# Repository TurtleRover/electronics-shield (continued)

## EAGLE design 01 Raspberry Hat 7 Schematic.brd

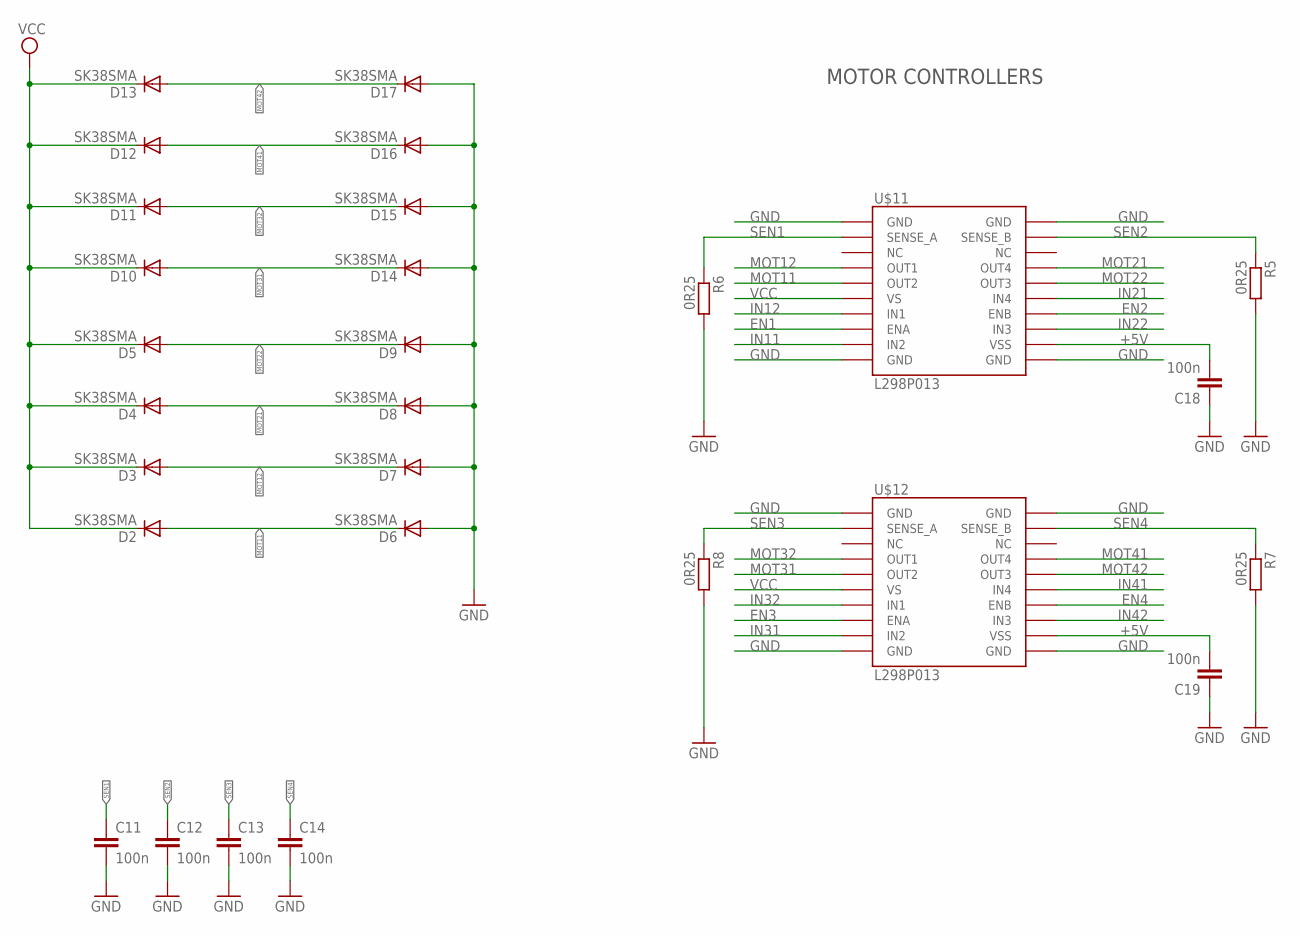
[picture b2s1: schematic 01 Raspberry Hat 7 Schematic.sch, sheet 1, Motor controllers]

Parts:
C11, C12, C13, C14, C18, C19: 100n; C0603K
D2, D3, D4, D5, D6, D7, D8, D9, D10, D11, D12, D13, D14, D15, D16, D17: SK38SMA; SOD123
R5, R6, R7, R8: 0R25; R2512
U$11, U$12: L298P013; POWERSO20

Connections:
+5V: C18.2, C19.2, U$11.12 (VSS), U$12.12 (VSS); also elsewhere on the board
EN1: U$11.8 (ENA); also elsewhere on the board
EN2: U$11.14 (ENB); also elsewhere on the board
EN3: U$12.8 (ENA); also elsewhere on the board
EN4: U$12.14 (ENB); also elsewhere on the board
GND: C11.2, C12.2, C13.2, C14.2, C18.1, C19.1, D6.A, D7.A, D8.A, D9.A, D14.A, D15.A, D16.A, D17.A, R5.2, R6.2, R7.2, R8.2, U$11.1 (GND), U$11.10 (GND), U$11.11 (GND), U$11.20 (GND), U$12.1 (GND), U$12.10 (GND), U$12.11 (GND), U$12.20 (GND); also elsewhere on the board
IN11: U$11.9 (IN2); also elsewhere on the board
IN12: U$11.7 (IN1); also elsewhere on the board
IN21: U$11.15 (IN4); also elsewhere on the board
IN22: U$11.13 (IN3); also elsewhere on the board
IN31: U$12.9 (IN2); also elsewhere on the board
IN32: U$12.7 (IN1); also elsewhere on the board
IN41: U$12.15 (IN4); also elsewhere on the board
IN42: U$12.13 (IN3); also elsewhere on the board
MOT11: D2.A, D6.C, U$11.5 (OUT2); also elsewhere on the board
MOT12: D3.A, D7.C, U$11.4 (OUT1); also elsewhere on the board
MOT21: D4.A, D8.C, U$11.17 (OUT4); also elsewhere on the board
MOT22: D5.A, D9.C, U$11.16 (OUT3); also elsewhere on the board
MOT31: D10.A, D14.C, U$12.5 (OUT2); also elsewhere on the board
MOT32: D11.A, D15.C, U$12.4 (OUT1); also elsewhere on the board
MOT41: D12.A, D16.C, U$12.17 (OUT4); also elsewhere on the board
MOT42: D13.A, D17.C, U$12.16 (OUT3); also elsewhere on the board
SEN1: C11.1, R6.1, U$11.2 (SENSE_A); also elsewhere on the board
SEN2: C12.1, R5.1, U$11.19 (SENSE_B); also elsewhere on the board
SEN3: C13.1, R8.1, U$12.2 (SENSE_A); also elsewhere on the board
SEN4: C14.1, R7.1, U$12.19 (SENSE_B); also elsewhere on the board
VCC: D2.C, D3.C, D4.C, D5.C, D10.C, D11.C, D12.C, D13.C, U$11.6 (VS), U$12.6 (VS); also elsewhere on the board

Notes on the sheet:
MOTOR CONTROLLERS

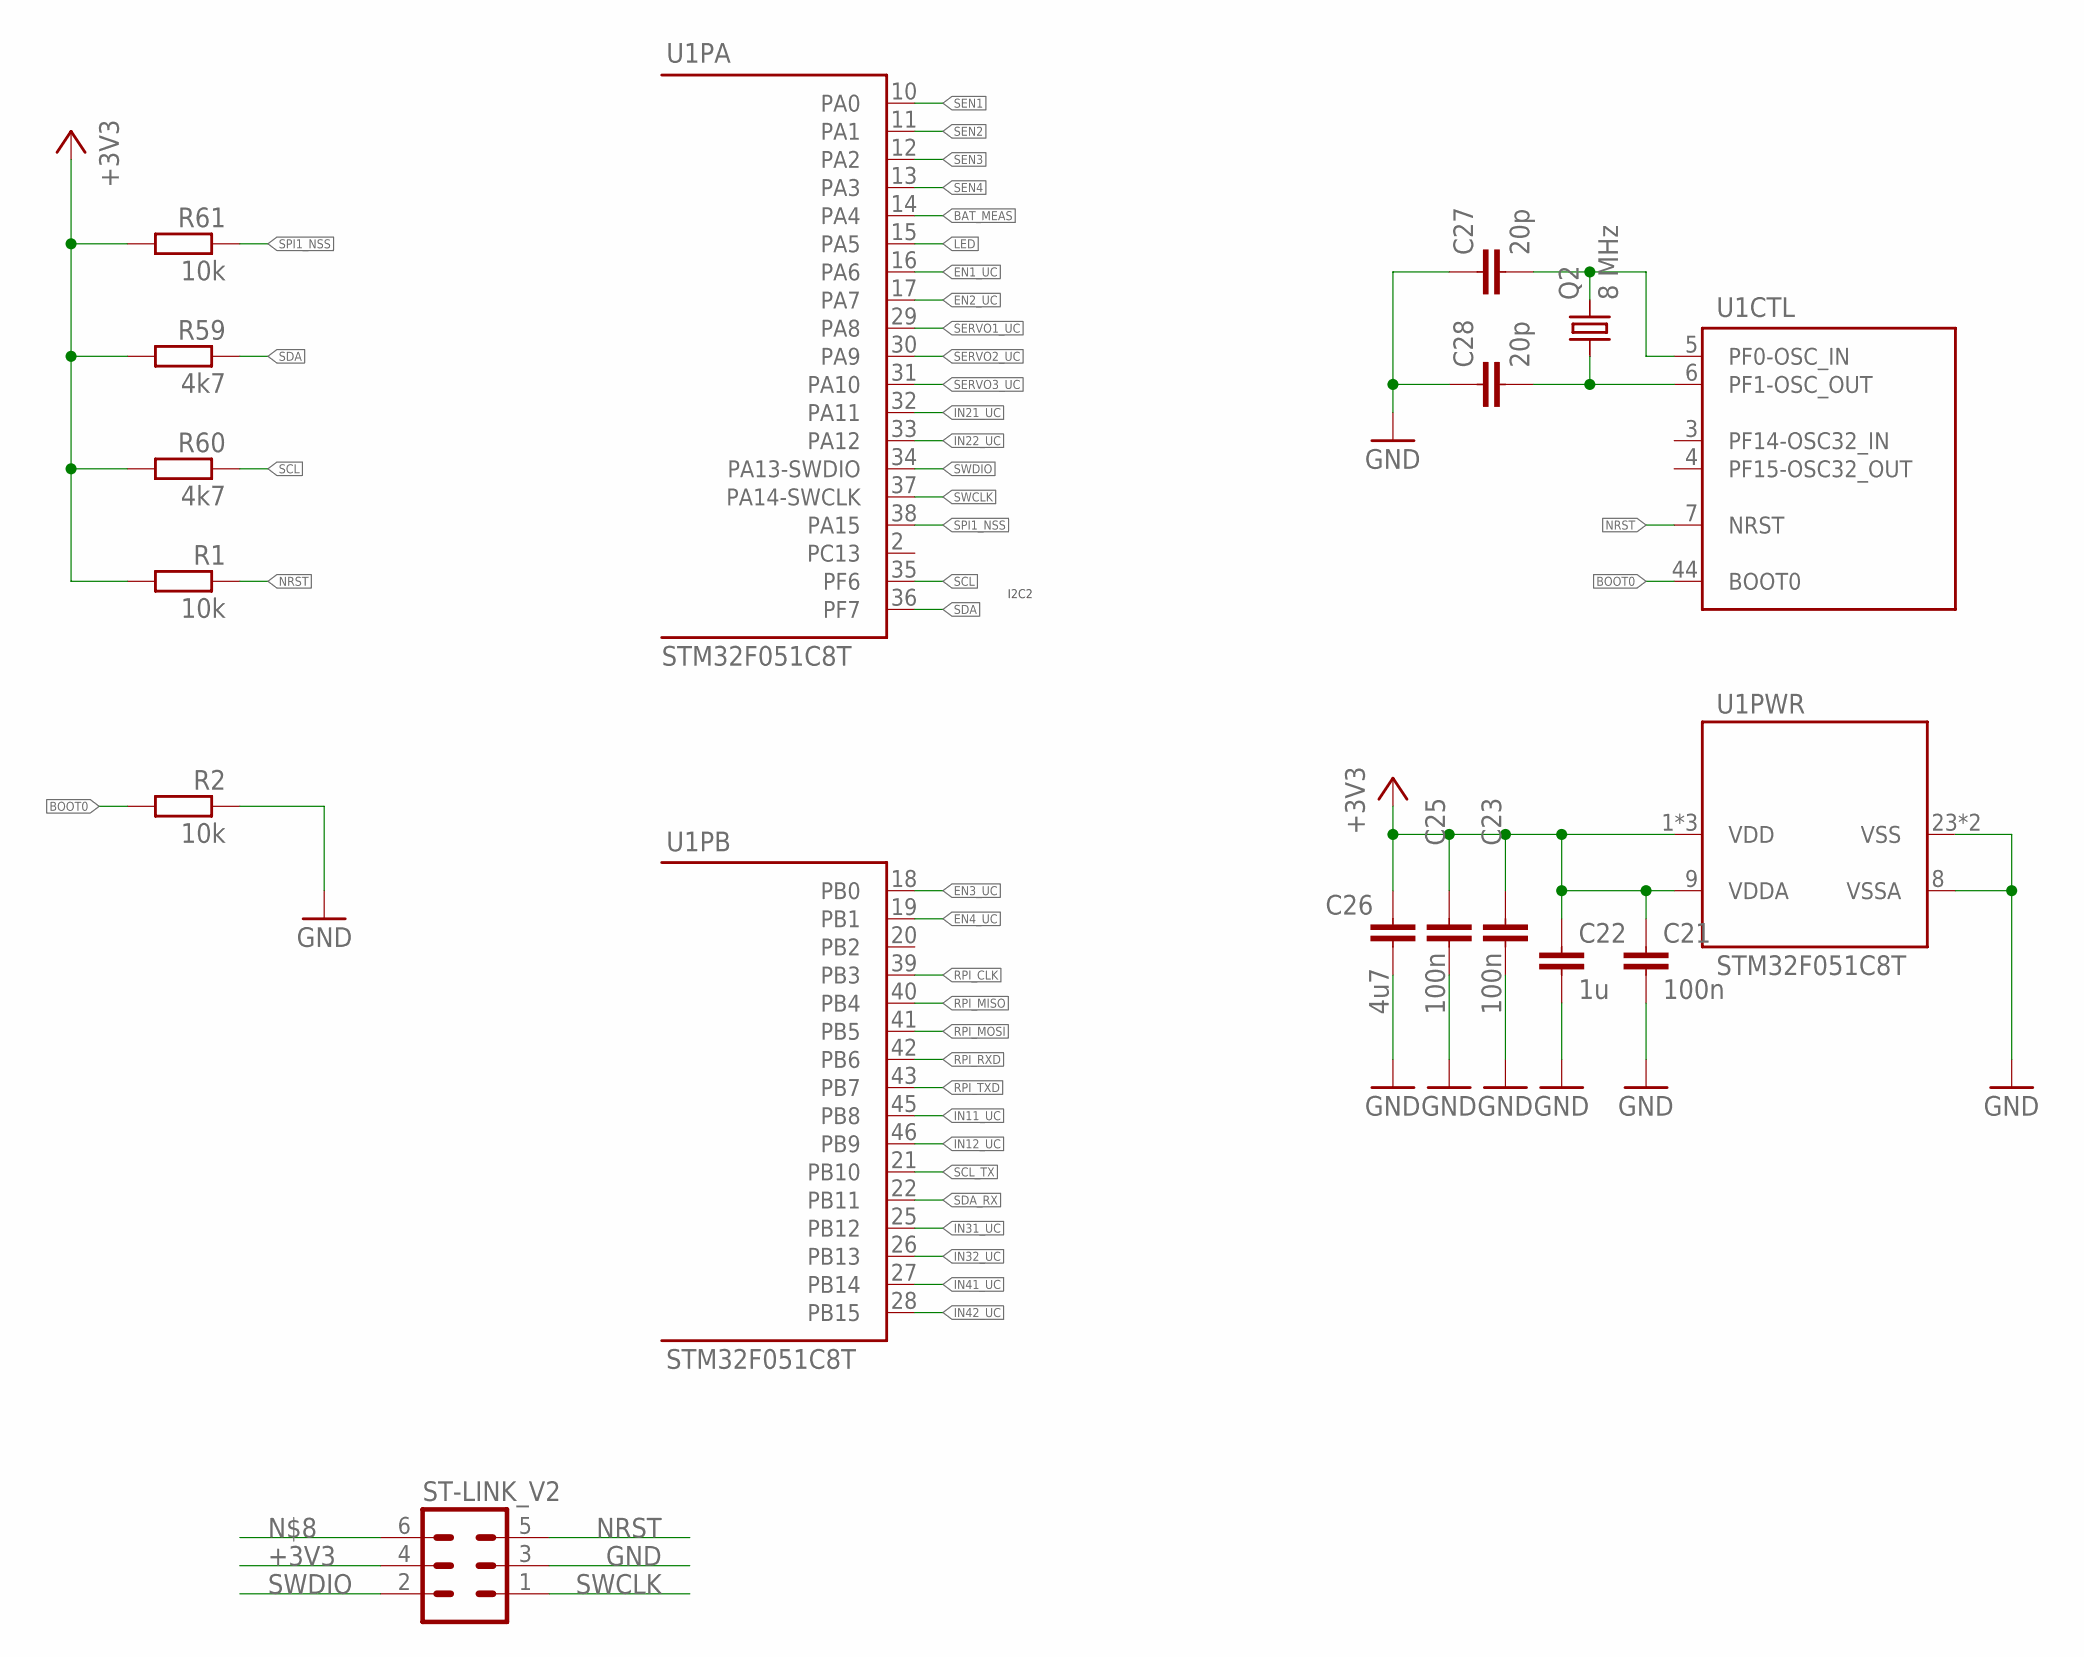
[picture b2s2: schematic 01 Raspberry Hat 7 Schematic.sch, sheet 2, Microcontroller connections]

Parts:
C21, C23, C25: 100n; C0603K
C22: 1u; C0603K
C26: 4u7; C0603K
C27, C28: 20p; C0603K
Q2: 8 MHz; HC49UP
R1, R2, R61: 10k; R0603
R59, R60: 4k7; R0603
ST-LINK_V2: ML6
U1: STM32F051C8T; LQFP48

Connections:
+3V3: C21.1, C22.1, C23.1, C25.1, C26.1, R1.2, R59.2, R60.2, R61.2, ST-LINK_V2.4, U1.1 (VDD), U1.9 (VDDA), U1.24 (VDD), U1.48 (VDD); also elsewhere on the board
BAT_MEAS: U1.14 (PA4); also elsewhere on the board
BOOT0: R2.2, U1.44 (BOOT0)
EN1_UC: U1.16 (PA6); also elsewhere on the board
EN2_UC: U1.17 (PA7); also elsewhere on the board
EN3_UC: U1.18 (PB0); also elsewhere on the board
EN4_UC: U1.19 (PB1); also elsewhere on the board
GND: C21.2, C22.2, C23.2, C25.2, C26.2, C27.1, C28.1, R2.1, ST-LINK_V2.3, U1.8 (VSSA), U1.23 (VSS), U1.47 (VSS); also elsewhere on the board
IN11_UC: U1.45 (PB8); also elsewhere on the board
IN12_UC: U1.46 (PB9); also elsewhere on the board
IN21_UC: U1.32 (PA11); also elsewhere on the board
IN22_UC: U1.33 (PA12); also elsewhere on the board
IN31_UC: U1.25 (PB12); also elsewhere on the board
IN32_UC: U1.26 (PB13); also elsewhere on the board
IN41_UC: U1.27 (PB14); also elsewhere on the board
IN42_UC: U1.28 (PB15); also elsewhere on the board
LED: U1.15 (PA5)
unnamed: C28.2, Q2.1, U1.6 (PF1-OSC_OUT)
unnamed: C27.2, Q2.2, U1.5 (PF0-OSC_IN)
NRST: R1.1, ST-LINK_V2.5, U1.7 (NRST); also elsewhere on the board
RPI_CLK: U1.39 (PB3); also elsewhere on the board
RPI_MISO: U1.40 (PB4); also elsewhere on the board
RPI_MOSI: U1.41 (PB5); also elsewhere on the board
RPI_RXD: U1.42 (PB6); also elsewhere on the board
RPI_TXD: U1.43 (PB7); also elsewhere on the board
SCL: R60.1, U1.35 (PF6); also elsewhere on the board
SCL_TX: U1.21 (PB10); also elsewhere on the board
SDA: R59.1, U1.36 (PF7); also elsewhere on the board
SDA_RX: U1.22 (PB11); also elsewhere on the board
SEN1: U1.10 (PA0); also elsewhere on the board
SEN2: U1.11 (PA1); also elsewhere on the board
SEN3: U1.12 (PA2); also elsewhere on the board
SEN4: U1.13 (PA3); also elsewhere on the board
SERVO1_UC: U1.29 (PA8); also elsewhere on the board
SERVO2_UC: U1.30 (PA9); also elsewhere on the board
SERVO3_UC: U1.31 (PA10); also elsewhere on the board
SPI1_NSS: R61.1, U1.38 (PA15); also elsewhere on the board
SWCLK: ST-LINK_V2.1, U1.37 (PA14-SWCLK); also elsewhere on the board
SWDIO: ST-LINK_V2.2, U1.34 (PA13-SWDIO); also elsewhere on the board

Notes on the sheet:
I2C2

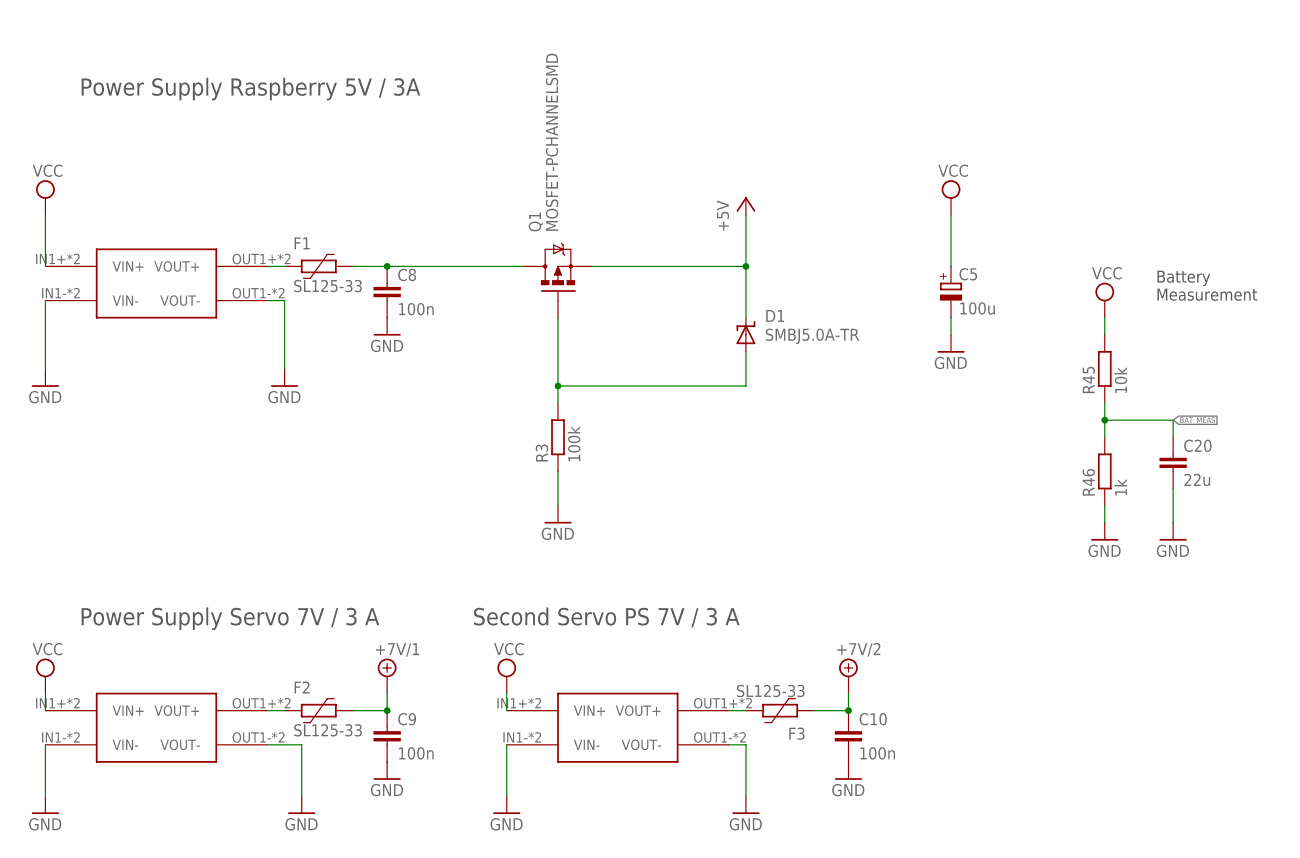
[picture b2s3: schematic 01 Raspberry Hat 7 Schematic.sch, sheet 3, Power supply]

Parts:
C5: 100u; 153CLV-0807
C8, C9, C10: 100n; C0603K
C20: 22u; C0603K
D1: SMBJ5.0A-TR; SMBJ
F1, F2, F3: SL125-33; 2920L
Q1: MOSFET-PCHANNELSMD; SOT23-3
R3: 100k; R0603
R45: 10k; R0603
R46: 1k; R0603
U$1, U$2, U$3: MP1584; DC-BRICK

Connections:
5V_NOT_TRIMMED: C8.1, F1.1, Q1.3 (D)
+5V: D1.C, Q1.2 (S); also elsewhere on the board
+5V_RAW: F1.2, U$3.OUT1+ (VOUT+), U$3.OUT2+ (VOUT+)
+7V/1: C9.1, F2.1; also elsewhere on the board
+7V/1_RAW: F2.2, U$2.OUT1+ (VOUT+), U$2.OUT2+ (VOUT+)
+7V/2: C10.1, F3.2; also elsewhere on the board
+7V/2_RAW: F3.1, U$1.OUT1+ (VOUT+), U$1.OUT2+ (VOUT+)
BAT_MEAS: C20.1, R45.1, R46.2; also elsewhere on the board
D1-R3: D1.A, Q1.1 (G), R3.2
GND: C5.-, C8.2, C9.2, C10.2, C20.2, R3.1, R46.1, U$1.IN1- (VIN-), U$1.IN2- (VIN-), U$1.OUT1- (VOUT-), U$1.OUT2- (VOUT-), U$2.IN1- (VIN-), U$2.IN2- (VIN-), U$2.OUT1- (VOUT-), U$2.OUT2- (VOUT-), U$3.IN1- (VIN-), U$3.IN2- (VIN-), U$3.OUT1- (VOUT-), U$3.OUT2- (VOUT-); also elsewhere on the board
VCC: C5.+, R45.2, U$1.IN1+ (VIN+), U$1.IN2+ (VIN+), U$2.IN1+ (VIN+), U$2.IN2+ (VIN+), U$3.IN1+ (VIN+), U$3.IN2+ (VIN+); also elsewhere on the board

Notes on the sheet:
Power Supply Raspberry 5V / 3A
Power Supply Servo 7V / 3 A
Second Servo PS 7V / 3 A
Battery Measurement

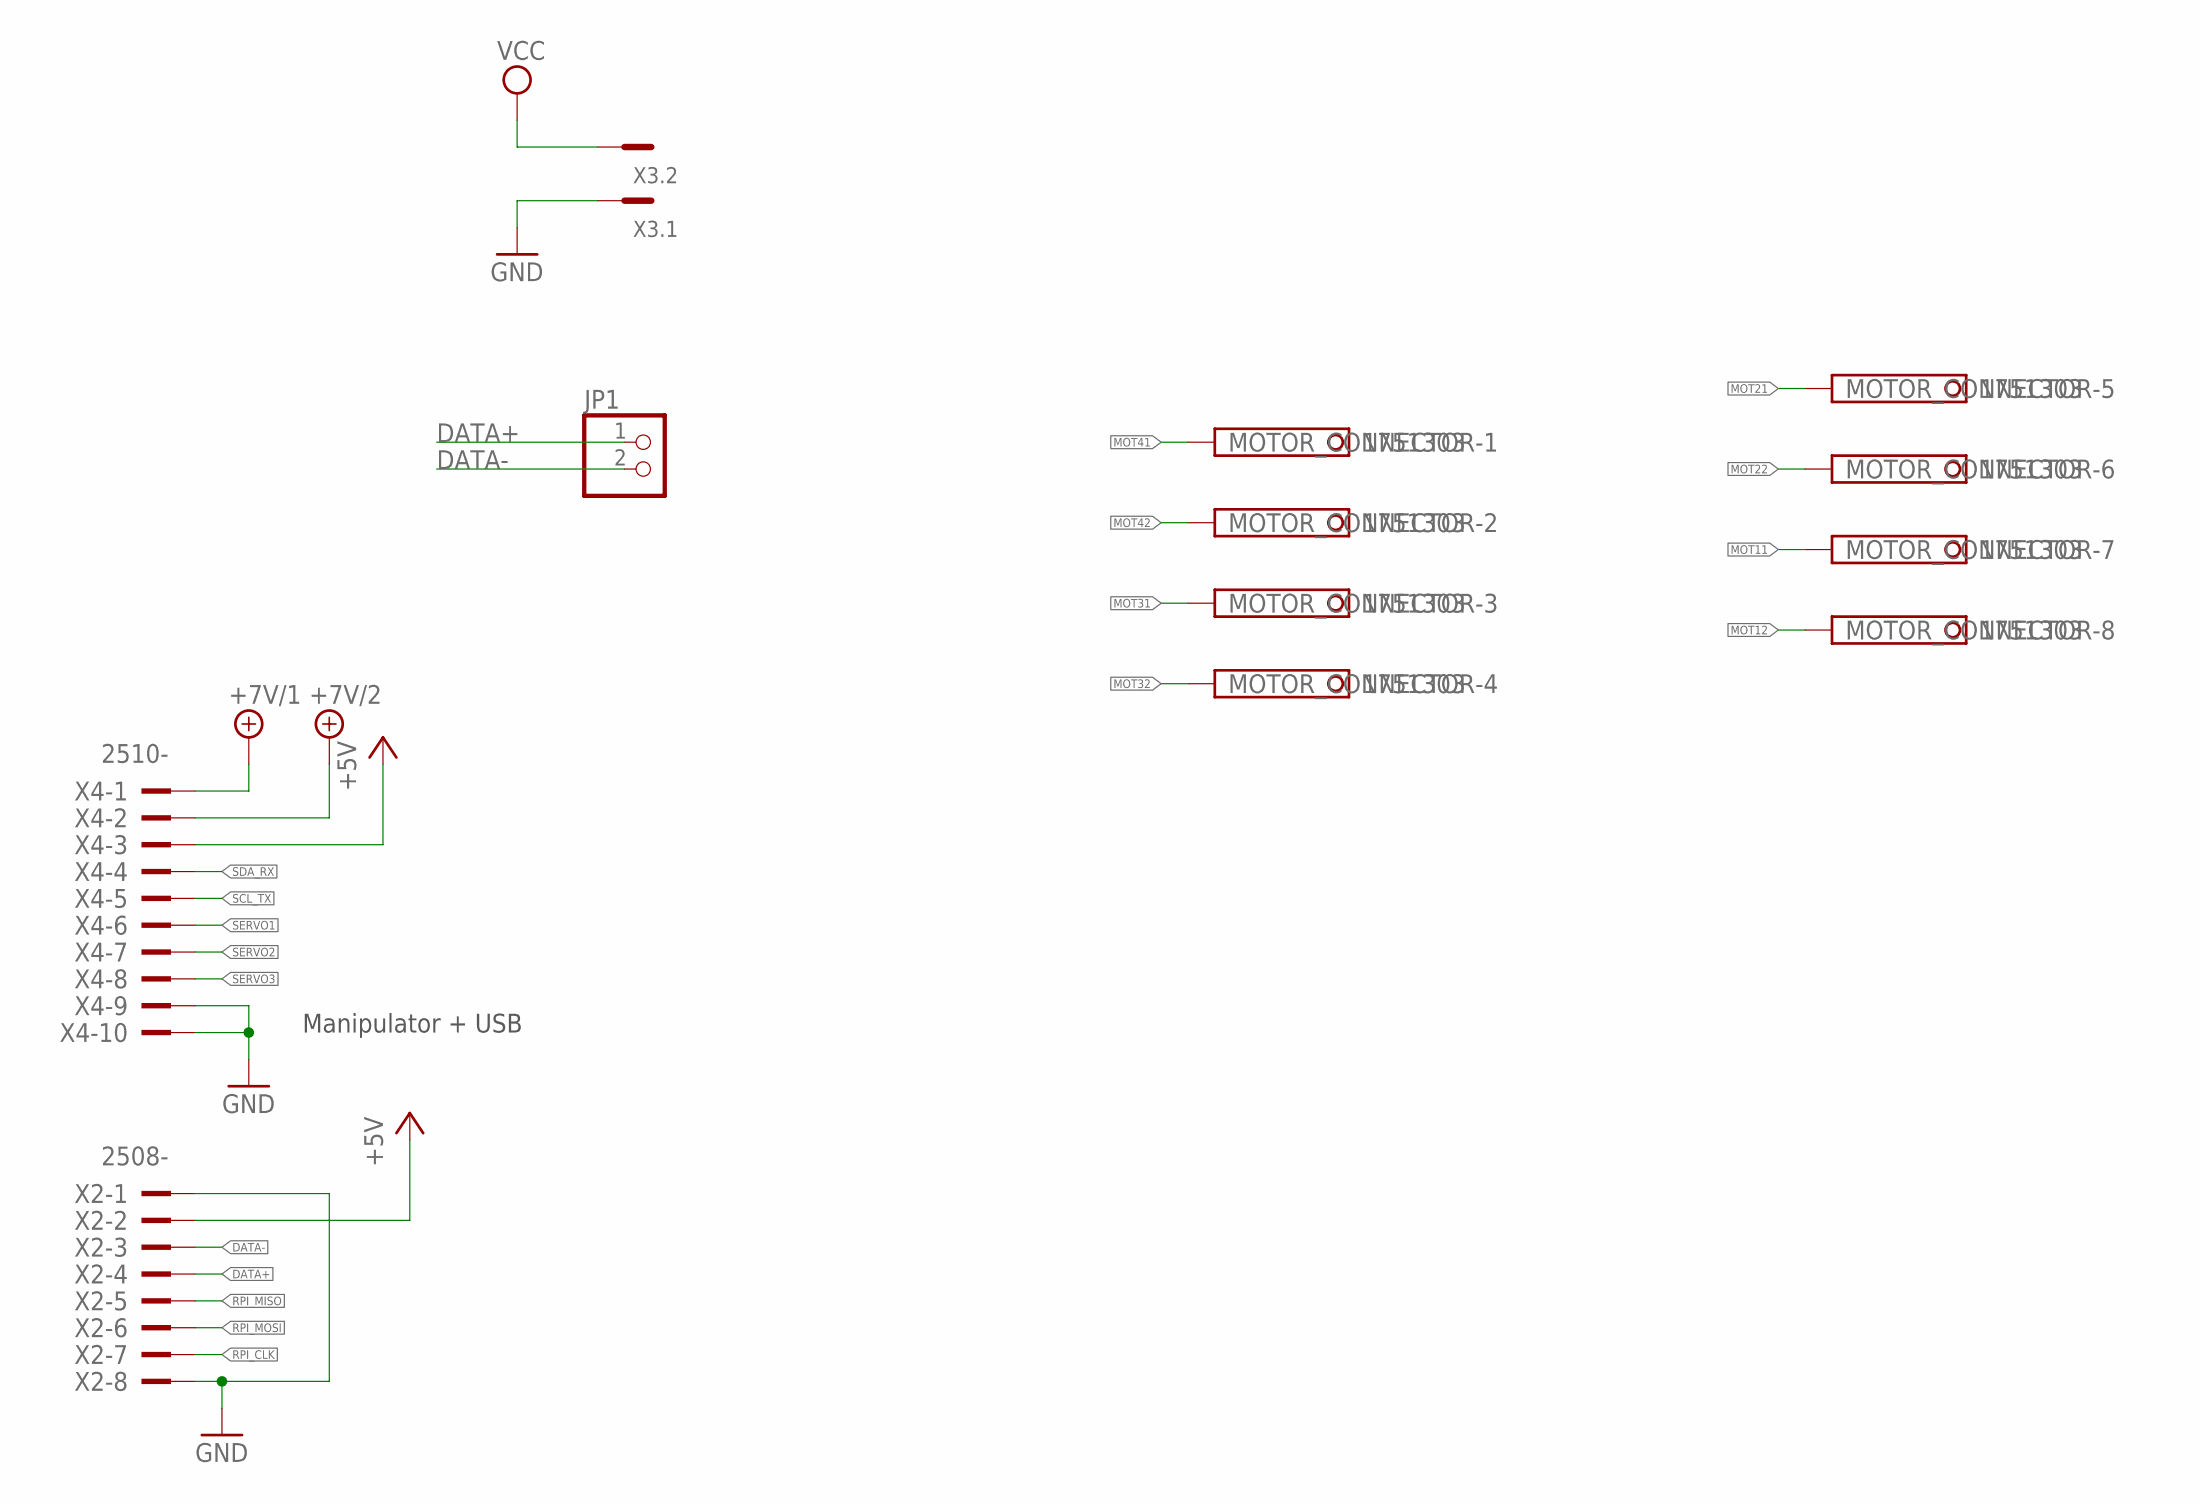
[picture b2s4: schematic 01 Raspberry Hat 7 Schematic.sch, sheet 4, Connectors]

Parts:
JP1: PINHD-1X2; 1X02
MOTOR_CONNECTOR: 1751303
X2: 2508-; PAK100/2500-10
X3: MC2
X4: 2510-; PAK100/2500-10

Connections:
+5V: X2.2, X4.3; also elsewhere on the board
+7V/1: X4.1; also elsewhere on the board
+7V/2: X4.2; also elsewhere on the board
DATA+: JP1.1, X2.4
DATA-: JP1.2, X2.3
GND: X2.1, X2.8, X3.1, X4.9, X4.10; also elsewhere on the board
MOT11: MOTOR_CONNECTOR.7; also elsewhere on the board
MOT12: MOTOR_CONNECTOR.8; also elsewhere on the board
MOT21: MOTOR_CONNECTOR.5; also elsewhere on the board
MOT22: MOTOR_CONNECTOR.6; also elsewhere on the board
MOT31: MOTOR_CONNECTOR.3; also elsewhere on the board
MOT32: MOTOR_CONNECTOR.4; also elsewhere on the board
MOT41: MOTOR_CONNECTOR.1; also elsewhere on the board
MOT42: MOTOR_CONNECTOR.2; also elsewhere on the board
RPI_CLK: X2.7; also elsewhere on the board
RPI_MISO: X2.5; also elsewhere on the board
RPI_MOSI: X2.6; also elsewhere on the board
SCL_TX: X4.5; also elsewhere on the board
SDA_RX: X4.4; also elsewhere on the board
SERVO1: X4.6; also elsewhere on the board
SERVO2: X4.7; also elsewhere on the board
SERVO3: X4.8; also elsewhere on the board
VCC: X3.2; also elsewhere on the board

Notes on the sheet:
Manipulator + USB

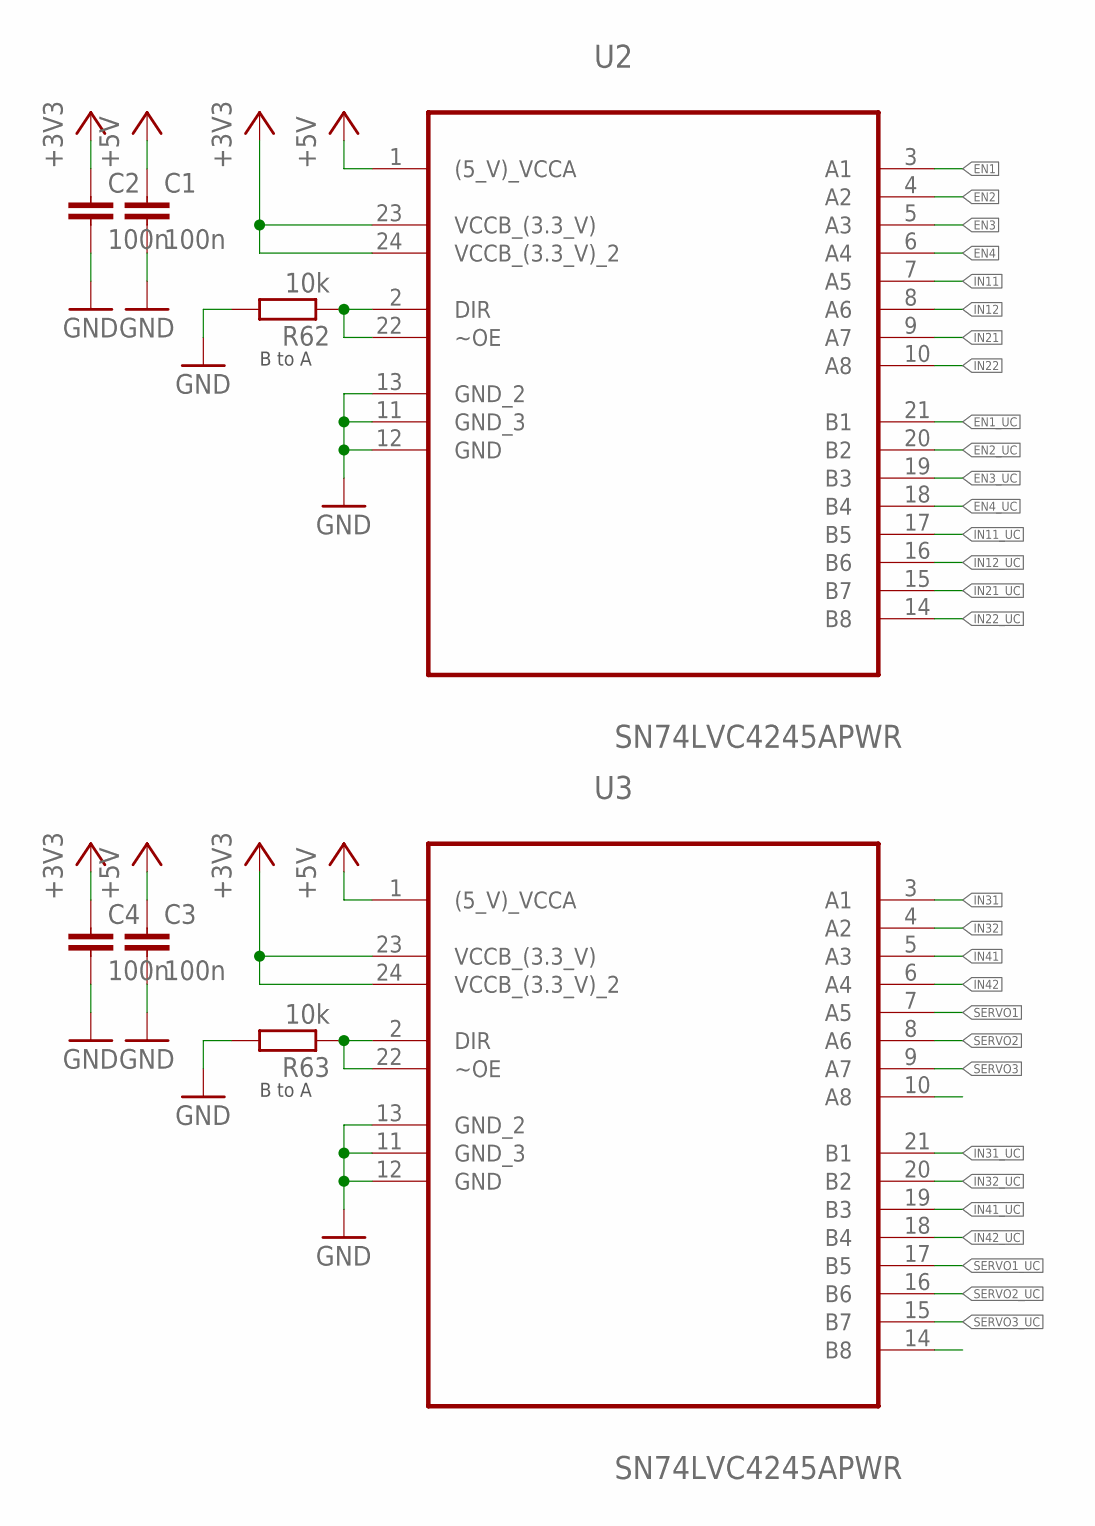
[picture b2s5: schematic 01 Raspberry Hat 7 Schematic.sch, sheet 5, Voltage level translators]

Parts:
C1, C2, C3, C4: 100n; C0603K
R62, R63: 10k; R0603
U2, U3: SN74LVC4245APWR; SOP65P640X120-24N

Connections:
+3V3: C2.1, C4.1, U2.23 (VCCB_(3.3_V)), U2.24 (VCCB_(3.3_V)_2), U3.23 (VCCB_(3.3_V)), U3.24 (VCCB_(3.3_V)_2); also elsewhere on the board
+5V: C1.1, C3.1, U2.1 ((5_V)_VCCA), U3.1 ((5_V)_VCCA); also elsewhere on the board
EN1: U2.3 (A1); also elsewhere on the board
EN1_UC: U2.21 (B1); also elsewhere on the board
EN2: U2.4 (A2); also elsewhere on the board
EN2_UC: U2.20 (B2); also elsewhere on the board
EN3: U2.5 (A3); also elsewhere on the board
EN3_UC: U2.19 (B3); also elsewhere on the board
EN4: U2.6 (A4); also elsewhere on the board
EN4_UC: U2.18 (B4); also elsewhere on the board
GND: C1.2, C2.2, C3.2, C4.2, R62.2, R63.2, U2.11 (GND_3), U2.12 (GND), U2.13 (GND_2), U3.11 (GND_3), U3.12 (GND), U3.13 (GND_2); also elsewhere on the board
IN11: U2.7 (A5); also elsewhere on the board
IN11_UC: U2.17 (B5); also elsewhere on the board
IN12: U2.8 (A6); also elsewhere on the board
IN12_UC: U2.16 (B6); also elsewhere on the board
IN21: U2.9 (A7); also elsewhere on the board
IN21_UC: U2.15 (B7); also elsewhere on the board
IN22: U2.10 (A8); also elsewhere on the board
IN22_UC: U2.14 (B8); also elsewhere on the board
IN31: U3.3 (A1); also elsewhere on the board
IN31_UC: U3.21 (B1); also elsewhere on the board
IN32: U3.4 (A2); also elsewhere on the board
IN32_UC: U3.20 (B2); also elsewhere on the board
IN41: U3.5 (A3); also elsewhere on the board
IN41_UC: U3.19 (B3); also elsewhere on the board
IN42: U3.6 (A4); also elsewhere on the board
IN42_UC: U3.18 (B4); also elsewhere on the board
unnamed: R62.1, U2.2 (DIR), U2.22 (~OE)
unnamed: R63.1, U3.2 (DIR), U3.22 (~OE)
SERVO1: U3.7 (A5); also elsewhere on the board
SERVO1_UC: U3.17 (B5); also elsewhere on the board
SERVO2: U3.8 (A6); also elsewhere on the board
SERVO2_UC: U3.16 (B6); also elsewhere on the board
SERVO3: U3.9 (A7); also elsewhere on the board
SERVO3_UC: U3.15 (B7); also elsewhere on the board

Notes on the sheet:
B to A

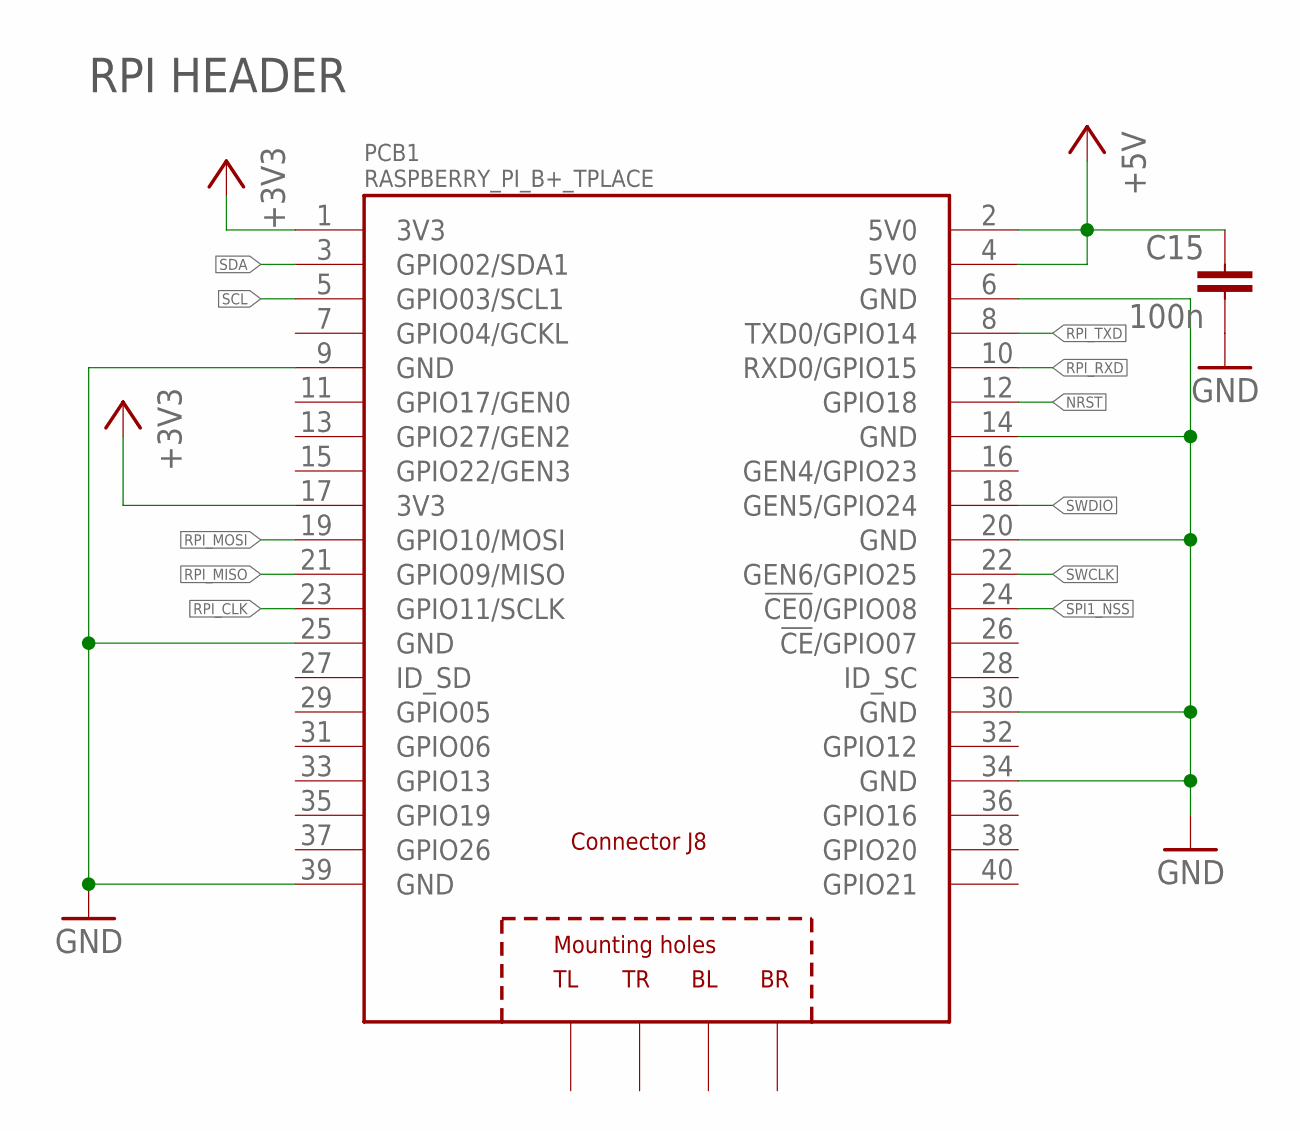
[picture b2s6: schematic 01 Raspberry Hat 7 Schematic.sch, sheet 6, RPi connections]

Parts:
C15: 100n; C0603K
PCB1: RASPBERRY_PI_B+_TPLACE; RASPBERRY_PI_BPLUS_TPLACE

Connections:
+3V3: PCB1.1 (3V3), PCB1.17 (3V3); also elsewhere on the board
+5V: C15.1, PCB1.2 (5V0), PCB1.4 (5V0); also elsewhere on the board
GND: C15.2, PCB1.6 (GND), PCB1.9 (GND), PCB1.14 (GND), PCB1.20 (GND), PCB1.25 (GND), PCB1.30 (GND), PCB1.34 (GND), PCB1.39 (GND); also elsewhere on the board
NRST: PCB1.12 (GPIO18); also elsewhere on the board
RPI_CLK: PCB1.23 (GPIO11/SCLK); also elsewhere on the board
RPI_MISO: PCB1.21 (GPIO09/MISO); also elsewhere on the board
RPI_MOSI: PCB1.19 (GPIO10/MOSI); also elsewhere on the board
RPI_RXD: PCB1.10 (RXD0/GPIO15); also elsewhere on the board
RPI_TXD: PCB1.8 (TXD0/GPIO14); also elsewhere on the board
SCL: PCB1.5 (GPIO03/SCL1); also elsewhere on the board
SDA: PCB1.3 (GPIO02/SDA1); also elsewhere on the board
SPI1_NSS: PCB1.24 (!CE0!/GPIO08); also elsewhere on the board
SWCLK: PCB1.22 (GEN6/GPIO25); also elsewhere on the board
SWDIO: PCB1.18 (GEN5/GPIO24); also elsewhere on the board

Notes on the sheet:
RPI HEADER

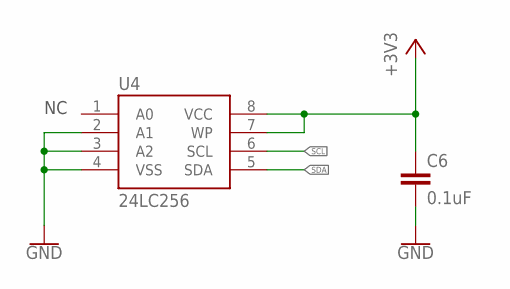
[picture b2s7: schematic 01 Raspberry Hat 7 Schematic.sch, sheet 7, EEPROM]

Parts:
C6: 0.1uF; C0603
U4: 24LC256; SO08

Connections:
+3V3: C6.1, U4.7 (WP), U4.8 (VCC); also elsewhere on the board
GND: C6.2, U4.2 (A1), U4.3 (A2), U4.4 (VSS); also elsewhere on the board
SCL: U4.6 (SCL); also elsewhere on the board
SDA: U4.5 (SDA); also elsewhere on the board

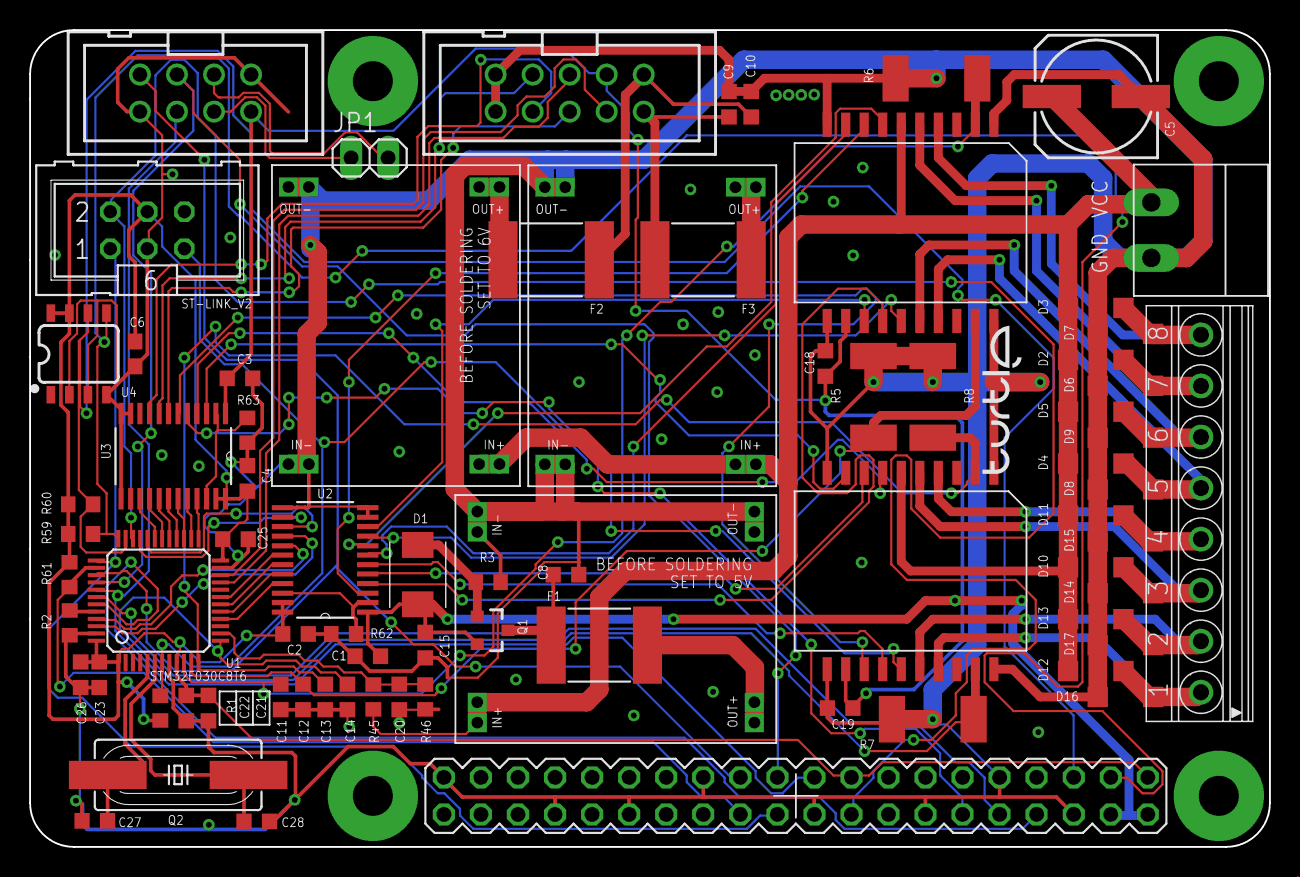
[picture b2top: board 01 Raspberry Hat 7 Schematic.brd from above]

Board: 2 copper layers, 85.0 x 56.0 mm, 76 parts (0 on the bottom side), 74 nets.
